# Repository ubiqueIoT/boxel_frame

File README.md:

# Boxel Frame
### Desktop Pixel Art Display

Pixel art has always struck a nostalgic chord. In an effort to perfect my workspace, I thought that a pixel art display case might be in order. This repository details the build process of my pixel frame. I tried to use as many off the shelf components as possible as to keep it easily reproducible.

OnShape was used to build the case for this project. You can find the project source [here](https://cad.onshape.com/documents/5000a3d49c7a9077d1572ff0/w/f60200444dc0dcea69f2e1f3/e/457eb17b8405f6b113c2318f?renderMode=0&uiState=63c5c0a977641842e2176192).
3D Prints were ordered from JLC PCB, using their SLA service with Black Resin. The STL files can be found in the 3D directory of this repository. 

KiCAD was used to make the adapter PCB. You can find the Gerber files in the PCB folder of this directory. The boards were ordered through [JLC PCB](https://jlcpcb.com/CWH).

The Seeed Studio [XIAO nRF52840](https://amzn.to/3kjpGdO) is used as the main processor. The [RP2040 variant](https://amzn.to/3kjpGdO) _should_ also work, but remains untested.

The display is a [240x240 TFT SPI module from Aliexpress](https://www.aliexpress.us/item/3256803574008408.html?spm=a2g0o.productlist.main.1.239917ddZtO2b2&algo_pvid=4f8b1cea-cd19-4f80-8319-a5b96f190500&algo_exp_id=4f8b1cea-cd19-4f80-8319-a5b96f190500-0&pdp_ext_f=%7B%22sku_id%22%3A%2212000027073447132%22%7D&pdp_npi=2%40dis%21USD%214.6%213.45%21%21%21%21%21%40211bd3cb16739046656243641d06d9%2112000027073447132%21sea&curPageLogUid=33Dx8JTfaZM6) 

An 8-pin right angle M-F header is required to attach the adapter PCB to the TFT display. 
Longer, [easily available, header rows](https://amzn.to/3Xi4Qdl) can be cut to size using snips.

As for assembly hardware, a few different lengths of M2 screws are used. 
All of these can be found in [an M2 hardware kit](https://amzn.to/3ZSZl6T).

- 4x 12mm M2 screw
- 1x 10mm M2 screw
- 2x 8mm M2 screw
- 7x M2 nut

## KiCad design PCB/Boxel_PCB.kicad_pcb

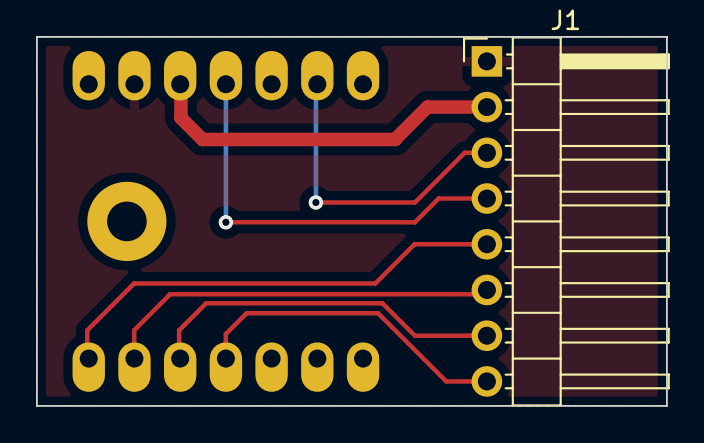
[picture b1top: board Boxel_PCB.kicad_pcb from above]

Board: 2 copper layers, 35.0 x 20.5 mm, 3 parts (0 on the bottom side), 8 nets.

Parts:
H1: MountingHole; MountingHole_2.2mm_M2_Pad
J1: Conn_01x08; PinHeader_1x08_P2.54mm_Horizontal
U1: SeeeduinoXIAO; xiao-tht

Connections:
+3V3: J1.2, U1.12 (3V3)
BLK: J1.8, U1.4 (PA11_A3_D3)
CS: J1.7, U1.3 (PA10_A2_D2)
DC: J1.6, U1.2 (PA4_A1_D1)
GND: J1.1, U1.13 (GND)
RES: J1.5, U1.1 (PA02_A0_D0)
SCL: J1.3, U1.9 (PA7_A8_D8_SCK)
SDA: J1.4, U1.11 (PA6_A10_D10_MOSI)

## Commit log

2023-01-16 PCB files
2023-01-16 STLs
2023-01-16 software
